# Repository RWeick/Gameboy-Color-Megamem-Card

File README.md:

# Gameboy-Color-Megamem-Card
All data necessary to produce a Mega Memory Card for the Gameboy Color. Be sure to use SLA Resin if you print the cartridge slot connector or the shells.

PCB Thickness: 0.8 mm

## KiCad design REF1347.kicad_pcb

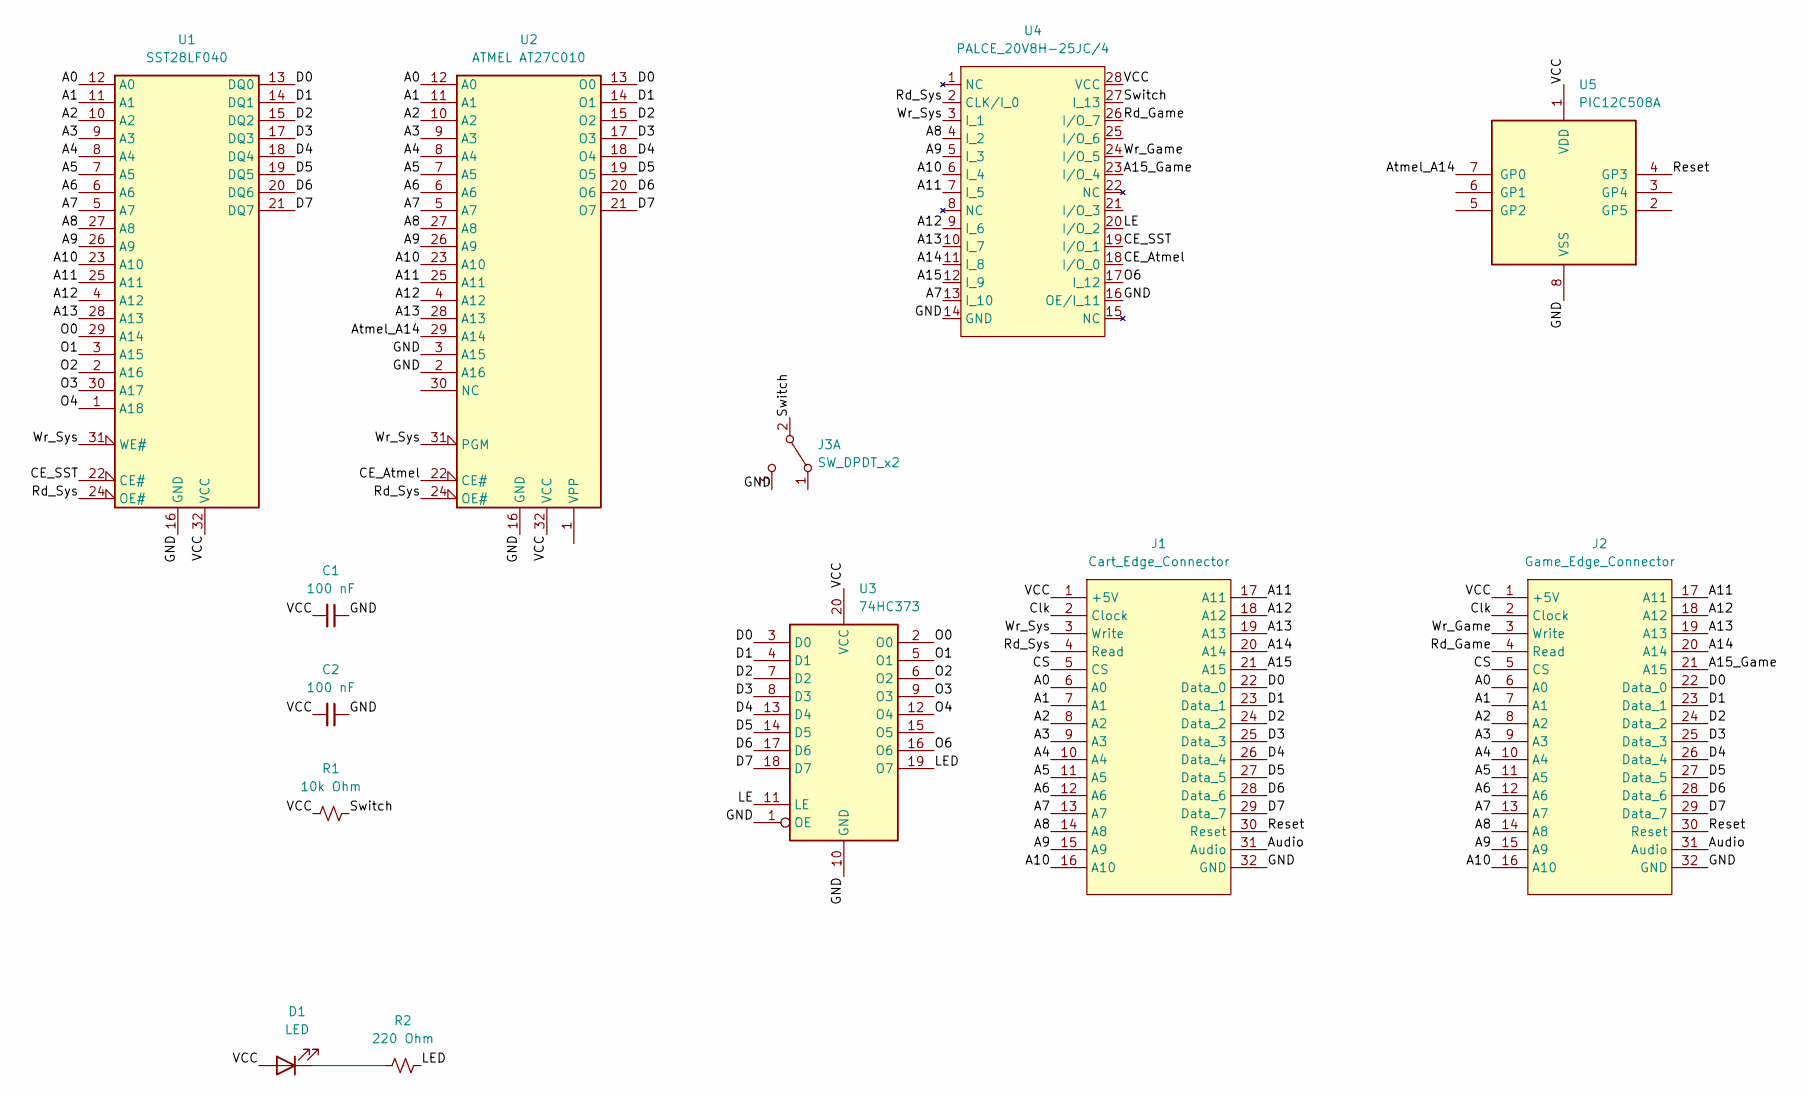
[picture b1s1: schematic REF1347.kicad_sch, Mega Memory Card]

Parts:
C1, C2: 100 nF; 100nf Capacitor
D1: LED; LED_D3.0mm
J1: Cart_Edge_Connector; ACTUAL GAMEBOY EDGE CONNECTOR
J2: Game_Edge_Connector; Cartridge Slot, GBC
J3: SW_DPDT_x2; Switch
R1: 10k Ohm; 100nf Capacitor
R2: 220 Ohm; 100nf Capacitor
U1: SST28LF040; SST 28SF040
U2: ATMEL AT27C010; SST 28SF040
U3: 74HC373
U4: PALCE_20V8H-25JC/4; PALCE 20V8H-25JC-4
U5: PIC12C508A

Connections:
/A0: J1.6 (A0), J2.6 (A0), U1.12 (A0), U2.12 (A0)
/A1: J1.7 (A1), J2.7 (A1), U1.11 (A1), U2.11 (A1)
/A2: J1.8 (A2), J2.8 (A2), U1.10 (A2), U2.10 (A2)
/A3: J1.9 (A3), J2.9 (A3), U1.9 (A3), U2.9 (A3)
/A4: J1.10 (A4), J2.10 (A4), U1.8 (A4), U2.8 (A4)
/A5: J1.11 (A5), J2.11 (A5), U1.7 (A5), U2.7 (A5)
/A6: J1.12 (A6), J2.12 (A6), U1.6 (A6), U2.6 (A6)
/A7: J1.13 (A7), J2.13 (A7), U1.5 (A7), U2.5 (A7), U4.13 (I_10)
/A8: J1.14 (A8), J2.14 (A8), U1.27 (A8), U2.27 (A8), U4.4 (I_2)
/A9: J1.15 (A9), J2.15 (A9), U1.26 (A9), U2.26 (A9), U4.5 (I_3)
/A10: J1.16 (A10), J2.16 (A10), U1.23 (A10), U2.23 (A10), U4.6 (I_4)
/A11: J1.17 (A11), J2.17 (A11), U1.25 (A11), U2.25 (A11), U4.7 (I_5)
/A12: J1.18 (A12), J2.18 (A12), U1.4 (A12), U2.4 (A12), U4.9 (I_6)
/A13: J1.19 (A13), J2.19 (A13), U1.28 (A13), U2.28 (A13), U4.10 (I_7)
/A14: J1.20 (A14), J2.20 (A14), U4.11 (I_8)
/A15: J1.21 (A15), U4.12 (I_9)
/A15_Game: J2.21 (A15), U4.23 (I/O_4)
/Atmel_A14: U2.29 (A14), U5.7 (GP0)
/Audio: J1.31 (Audio), J2.31 (Audio)
/CE_Atmel: U2.22 (CE#), U4.18 (I/O_0)
/CE_SST: U1.22 (CE#), U4.19 (I/O_1)
/CS: J1.5 (CS), J2.5 (CS)
/Clk: J1.2 (Clock), J2.2 (Clock)
/D0: J1.22 (Data_0), J2.22 (Data_0), U1.13 (DQ0), U2.13 (O0), U3.3 (D0)
/D1: J1.23 (Data_1), J2.23 (Data_1), U1.14 (DQ1), U2.14 (O1), U3.4 (D1)
/D2: J1.24 (Data_2), J2.24 (Data_2), U1.15 (DQ2), U2.15 (O2), U3.7 (D2)
/D3: J1.25 (Data_3), J2.25 (Data_3), U1.17 (DQ3), U2.17 (O3), U3.8 (D3)
/D4: J1.26 (Data_4), J2.26 (Data_4), U1.18 (DQ4), U2.18 (O4), U3.13 (D4)
/D5: J1.27 (Data_5), J2.27 (Data_5), U1.19 (DQ5), U2.19 (O5), U3.14 (D5)
/D6: J1.28 (Data_6), J2.28 (Data_6), U1.20 (DQ6), U2.20 (O6), U3.17 (D6)
/D7: J1.29 (Data_7), J2.29 (Data_7), U1.21 (DQ7), U2.21 (O7), U3.18 (D7)
/GND: C1.1, C2.1, J1.32 (GND), J2.32 (GND), J3.3 (C), U1.16 (GND), U2.2 (A16), U2.3 (A15), U2.16 (GND), U3.1 (OE), U3.10 (GND), U4.14 (GND), U4.16 (OE/I_11), U5.8 (VSS)
/LE: U3.11 (LE), U4.20 (I/O_2)
/LED: R2.1, U3.19 (O7)
/O0: U1.29 (A14), U3.2 (O0)
/O1: U1.3 (A15), U3.5 (O1)
/O2: U1.2 (A16), U3.6 (O2)
/O3: U1.30 (A17), U3.9 (O3)
/O4: U1.1 (A18), U3.12 (O4)
/O6: U3.16 (O6), U4.17 (I_12)
/Rd_Game: J2.4 (Read), U4.26 (I/O_7)
/Rd_Sys: J1.4 (Read), U1.24 (OE#), U2.24 (OE#), U4.2 (CLK/I_0)
/Reset: J1.30 (Reset), J2.30 (Reset), U5.4 (GP3)
/Switch: J3.2 (B), R1.1, U4.27 (I_13)
/VCC: C1.2, C2.2, D1.2 (A), J1.1 (+5V), J2.1 (+5V), R1.2, U1.32 (VCC), U2.32 (VCC), U3.20 (VCC), U4.28 (VCC), U5.1 (VDD)
/Wr_Game: J2.3 (Write), U4.24 (I/O_5)
/Wr_Sys: J1.3 (Write), U1.31 (WE#), U2.31 (PGM), U4.3 (I_1)
unnamed: D1.1 (K), R2.2

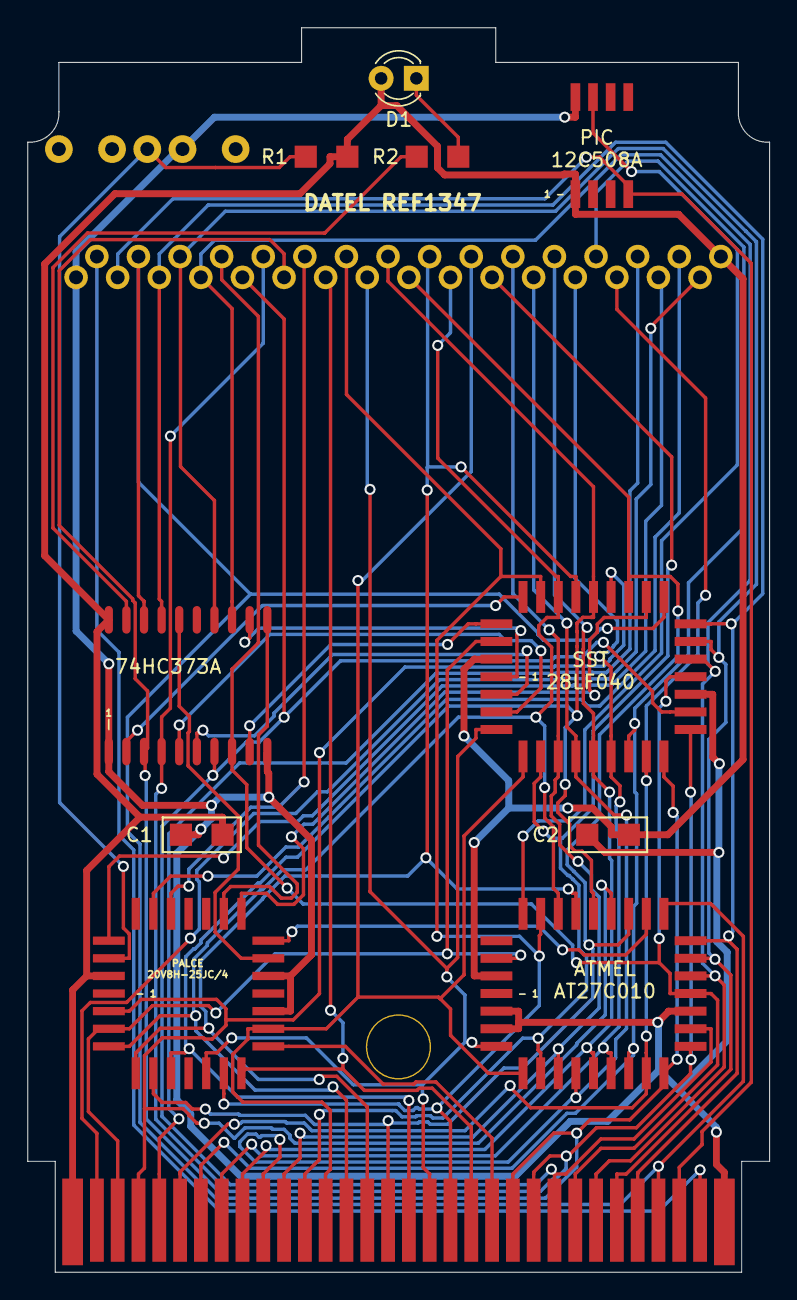
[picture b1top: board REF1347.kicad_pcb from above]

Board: 2 copper layers, 53.5 x 89.8 mm, 13 parts (0 on the bottom side), 48 nets.

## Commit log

2022-09-16 Add files via upload
    Corrected the edge connector to match the official Nintendo Gameboy footprint. Corrected a non-curved corner.
